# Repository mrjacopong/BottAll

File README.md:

# Welcome to BottAll :leaves:
<br>

Hello there!
This is **BottAll**,  a University Buisness Plan project created by some students of the master course of Electric Vehicle Engineering at [MUNER  University](https://motorvehicleuniversity.com).
Our idea won the first price at [**Bologna  Startup  Prize**  **chap V**  **2020**](https://www.facebook.com/bolognastartup): our buisness plan expressed the best growth potential above all, and it was particularly appreciated dueto its feasibility.

## What is the aim of this project :thinking:
BottAll was born as a project for the exam of the course of *Laboratory of Business Plan M*.
Starting from the idea of a new product which could be competitive on the market, we had to create a buisness plan around it. At the end of the course, we presented the whole project to our peers, the Professor and some experts in startups.

## What is BottAll? :fork_and_knife:
As the name can suggest, BottAll is an all-in-one packet lunch mate: it is a "bottle" composed by two part:

 - **Water can**: that can contain up to 0.5l of thermally insulated liquid;
 - **Food container**: with a capacity of 0.45l, it can contain food and it has also an integrated circuit that allows a connection with the smartphone. It can be plug with a usb-c charger to warm up the food.

More details can be found on the buisness plan or in our presentation.

## Why here on github? :octocat:
We think it is the best place to share our work, to the Open Source community, and to everyone who is interested in new engineering and design challenges.

## About us :heart::battery::racing_car:
We are master students from [EVE](https://motorvehicleuniversity.com/electric-vehicle-engineering/), with very different experiences and backgrounds. Let us introduce ourselves:

 - [Francesco Romani](https://www.linkedin.com/), b. 1998
	 - :books: MSc student in Electric Vehicle Engineering, MUNER 
	 -  :man_student: BSc in Energy Engineering, UNIPD​

 - [Mattia Davario](https://www.linkedin.com/in/mattia-davario-275609176), b. 1997
	 -  :books: MSc student in Electric Vehicle Engineering, MUNER
	 - :man_student: BSc in Electrical Engineering, UNIBO​

 - [Jacopo Ferretti](https://www.linkedin.com/in/jacopoferretti/), b. 1998
	 - :books: MSc student in Electric Vehicle Engineering, MUNER
	 - :racing_car: Ex member of Formula Student project of University of Ancona
	 - :man_student: BSc in Computer and Automation Engineering at UNIVPM

 - [Tommaso Bertoncello​](https://www.linkedin.com/in/tommaso-bertoncello), b. 1998
	 - :books: MSc student in Electric Vehicle Engineering, MUNER
	 - :man_student: BSc in Energy Engineering, UNIPD​

 - [Rosario La Rocca​](https://www.linkedin.com/in/rosario-la-rocca), b. 1995
	 - :books: MSc student in Electric Vehicle Engineering, MUNER
	 - :racing_car: Ex member of Formula Student project of University of Bologna
	 - :man_student: BSc in Electrical Engineering, UNIBO​

## How to compile the latex package:
Please use **LuaLatex**.
###  note :exclamation: 
We don't really know why, but the compiler is giving an error about the *'caption' package*, here it is the log:

```plaintext
! Package caption Error: hang undefined.
See the caption package documentation for explanation.
Type H <return> for immediate help.
...
l.33 \DeclareCaptionFormat
{upper}{#1#2\uppercase{#3}\par}
If you do not understand this error, please take a closer look
at the documentation of the `caption' package, especially the
section about errors.
```
Despite this, the output pdf should look normal, so you can neglect it.

## License
<p xmlns:cc="http://creativecommons.org/ns#" xmlns:dct="http://purl.org/dc/terms/"><a property="dct:title" rel="cc:attributionURL" href="https://github.com">BottAll</a> by <span property="cc:attributionName">F. Romani, M. Davario, J. Ferretti, T. Bertoncello, R. La Rocca</span> is licensed under <a href="http://creativecommons.org/licenses/by-nc/4.0/?ref=chooser-v1" target="_blank" rel="license noopener noreferrer" style="display:inline-block;">CC BY-NC 4.0</a></p>

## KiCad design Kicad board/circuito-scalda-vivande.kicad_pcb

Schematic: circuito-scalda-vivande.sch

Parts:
C1, C4: 100n; C_0603_1608Metric
C2: 22µF; C_0603_1608Metric
C3: 10µF; C_0603_1608Metric
H2, H3, H4: MountingHole; MountingHole_2.2mm_M2_Pad_Via
IC1: AZ1117IH-3.3TRG1; SOT230P700X180-4N; Mouser Part Number 621-AZ1117IH-3.3TRG1
J1: USB4085-GF-A_REVA; GCT_USB4085-GF-A_REVA
J2: Temp sensor connector; SHDR2W50P0X200_1X2_600X470X635P
LED1: 521-8559F; 5218559F; Mouser Part Number 645-5218559F
Q1: IRL540NSTRLPBF; D2PAK; Mouser Part Number 942-IRL540NSTRLPBF
R1, R4, R5: 1k; R_0603_1608Metric
R3: 250; R_0603_1608Metric
R6: PWR221T-30-1R50F; TO508P343X1041X1930-2P; Mouser Part Number 652-PWR221T-30-1R50F
R7: 420ohm; R_0603_1608Metric
U1: ESP32-WROOM-32D; ESP32-WROOM-32

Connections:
3.3V: C2.1, C4.1, IC1.2 (OUTPUT), R1.2, R4.2, U1.2 (VDD), U1.3 (EN)
5V: C1.1, C3.2, J1.A4 (VBUS), J1.A9 (VBUS), J1.B4 (VBUS), J1.B9 (VBUS), R6.2
GND: C1.2, C2.2, C4.2, IC1.1 (ADJ/GND), J1.A1 (GND), J1.A12 (GND), J1.B1 (GND), J1.B12 (GND), J1.P1 (SHELL), J1.P2 (SHELL), J1.P3 (SHELL), J1.P4 (SHELL), J2.2, Q1.2, R3.2, R5.1, U1.1 (GND), U1.15 (GND), U1.38 (GND), U1.39 (GND)
unnamed: C3.1, IC1.3 (INPUT)
unnamed: J2.1, R1.1, U1.11 (IO26)
unnamed: LED1.1 (RED_K), U1.9 (IO33)
unnamed: LED1.2 (COMMON_A), R3.1
unnamed: LED1.3 (BLUE_K), U1.7 (IO35)
unnamed: LED1.4 (GREEN_K), U1.6 (IO34)
unnamed: Q1.1, R7.1
unnamed: Q1.3, R6.1
unnamed: R4.1, R5.2, U1.12 (IO27)
unnamed: R7.2, U1.8 (IO32)

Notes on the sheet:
tepmerature sensor: 10k NTC

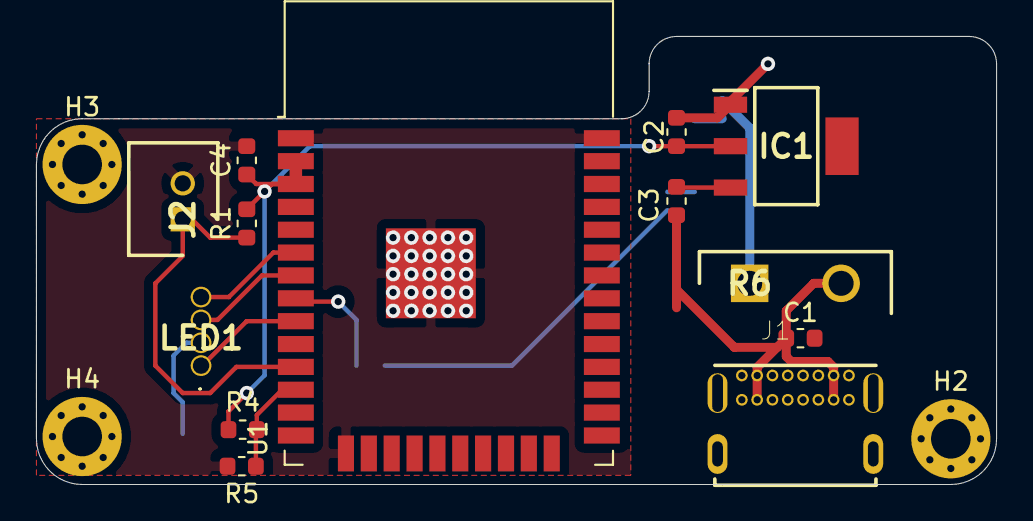
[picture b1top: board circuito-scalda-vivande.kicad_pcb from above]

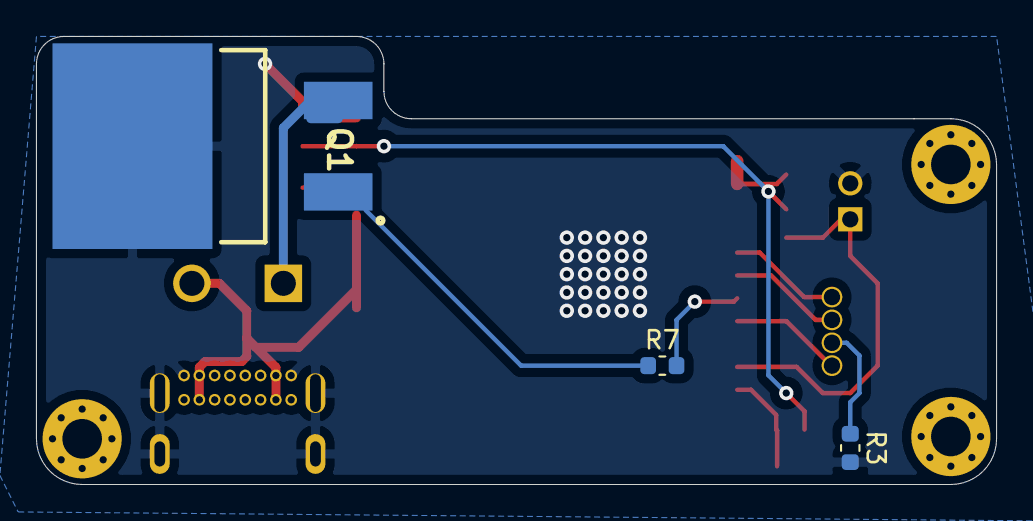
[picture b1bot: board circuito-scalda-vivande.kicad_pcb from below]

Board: 2 copper layers, 53.3 x 24.9 mm, 19 parts (3 on the bottom side), 13 nets.

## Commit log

2021-07-22 first commit.
